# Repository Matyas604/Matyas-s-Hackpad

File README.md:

# Matyas-s-Hackpad
It has 8 keys (7 switches + rotary encoder switch), a rotary encoder, and an OLED display. Each key is backlit with SK6812 MINI-E LEDs. It uses [QMK](https://qmk.fm/) firmware and VIA.

## CAD Model:
Everything is connected by four M3x16mm screws and M3x5mx4mm heatset inserts. The case is printed in two parts, top and bottom.

<p align="center">
  <strong>Made in Fusion360</strong>
</p>

## PCB:
<p align="center">
  Schematic
</p>

<br>
<p align="center">
  PCB
</p>

<p align="center">
  <strong>Made in KiCad</strong>
</p>

## Case:

<p align="center">
  <strong>Made in Fusion360</strong>
</p>

## Firmware:
This Hackpad uses [QMK](https://qmk.fm/) firmware. Everything can be controlled in VIA. I have five layers set up, and I can assign anything to each one. I switch between them with a single switch. My layers are Main, Media, HA (shortcuts for Home Assistant), Game, and Other. I can also adjust the effects, speed, brightness, and backlight colors of LEDs directly from VIA. The OLED display shows the name of the current page.

## Final result:

<p align="center">
  <a href="https://www.youtube.com/shorts/VJYHFeJ_mRk">
    🎬 <b>HACKPAD DEMO HERE</b> 🎬
  </a>
</p>
I really enjoyed designing and building the hackpad. It was the very first project I designed from start to finish. I learned how to use Fusion and create PCBs in KiCAD. There were a few mistakes in the model, but they weren’t that big. I made only one mistake during assembly: I soldered the rotary encoder on the other side of the board, and when I desoldered it, I snapped off a leg, but there were two in the kit, so it was fine. The programming was a bit difficult, but in the end, I managed to do what I wanted. 

## BOM:
Here is everything you need to create this Hackpad:
| Component | Amount |
| :--- | :---: |
| **Seeed XIAO RP2040** | 1x |
| **MX-Style switches** | 7x |
| **1N4148 Diodes** | 8x | 
| **EC11 Rotary encoder** | 1x |
| **0.91 inch OLED display** | 1x |
| **DSA keycaps** | 7x |
| **SK6812 MINI-E LED** | 7x |
| **M3x16mm screw** | 4x |
| **M3x5mx4mm heatset insert** | 4x |
| **Case** (2 printed parts) | 1x |
| **PCB** | 1x |

<hr>

<p align="center">
  Made with ❤️ by <a href="https://github.com/Matyas604">@Matyas604</a>
</p>

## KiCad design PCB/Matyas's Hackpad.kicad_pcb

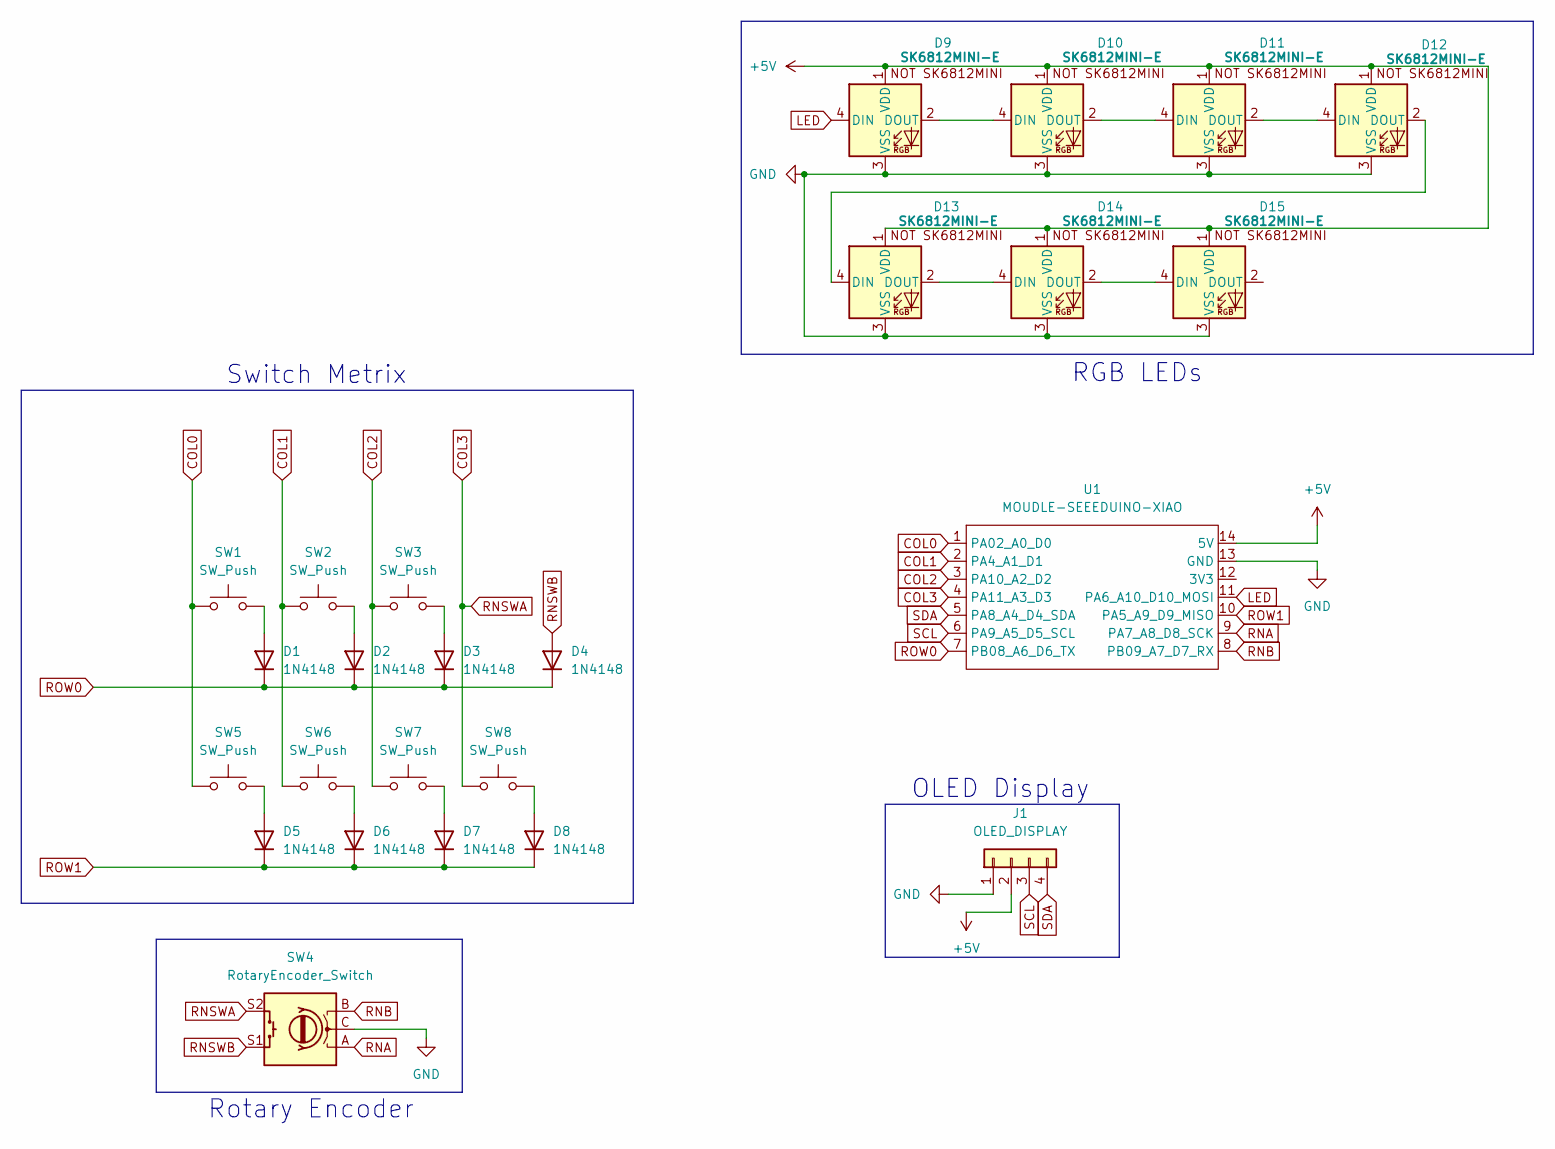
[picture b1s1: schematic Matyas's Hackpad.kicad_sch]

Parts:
D1, D2, D3, D4, D5, D6, D7, D8: 1N4148; D_DO-35_SOD27_P7.62mm_Horizontal
D9, D10, D11, D12, D13, D14, D15: SK6812MINI-E; SK6812MINI-E_fixed
J1: OLED_DISPLAY; SSD1306-0.91-OLED-4pin-128x32
SW1, SW2, SW3, SW5, SW6, SW7, SW8: SW_Push; SW_Cherry_MX_1.00u_PCB
SW4: RotaryEncoder_Switch; RotaryEncoder_Alps_EC11E-Switch_Vertical_H20mm
U1: MOUDLE-SEEEDUINO-XIAO; XIAO-Generic-Hybrid-14P-2.54-21X17.8MM

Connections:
+5V: D9.1 (VDD), D10.1 (VDD), D11.1 (VDD), D12.1 (VDD), D13.1 (VDD), D14.1 (VDD), D15.1 (VDD), J1.2, U1.14 (5V)
COL0: SW1.1, SW5.1, U1.1 (PA02_A0_D0)
COL1: SW2.1, SW6.1, U1.2 (PA4_A1_D1)
COL2: SW3.1, SW7.1, U1.3 (PA10_A2_D2)
COL3: SW4.S2, SW8.1, U1.4 (PA11_A3_D3)
GND: D9.3 (VSS), D10.3 (VSS), D11.3 (VSS), D12.3 (VSS), D13.3 (VSS), D14.3 (VSS), D15.3 (VSS), J1.1, SW4.C, U1.13 (GND)
LED: D9.4 (DIN), U1.11 (PA6_A10_D10_MOSI)
unnamed: D1.2 (A), SW1.2
unnamed: D2.2 (A), SW2.2
unnamed: D3.2 (A), SW3.2
unnamed: D5.2 (A), SW5.2
unnamed: D6.2 (A), SW6.2
unnamed: D7.2 (A), SW7.2
unnamed: D8.2 (A), SW8.2
unnamed: D9.2 (DOUT), D10.4 (DIN)
unnamed: D10.2 (DOUT), D11.4 (DIN)
unnamed: D11.2 (DOUT), D12.4 (DIN)
unnamed: D12.2 (DOUT), D13.4 (DIN)
unnamed: D13.2 (DOUT), D14.4 (DIN)
unnamed: D14.2 (DOUT), D15.4 (DIN)
RNA: SW4.A, U1.9 (PA7_A8_D8_SCK)
RNB: SW4.B, U1.8 (PB09_A7_D7_RX)
RNSWB: D4.2 (A), SW4.S1
ROW0: D1.1 (K), D2.1 (K), D3.1 (K), D4.1 (K), U1.7 (PB08_A6_D6_TX)
ROW1: D5.1 (K), D6.1 (K), D7.1 (K), D8.1 (K), U1.10 (PA5_A9_D9_MISO)
SCL: J1.3, U1.6 (PA9_A5_D5_SCL)
SDA: J1.4, U1.5 (PA8_A4_D4_SDA)

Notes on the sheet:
RGB LEDs
Switch Metrix
OLED Display
Rotary Encoder

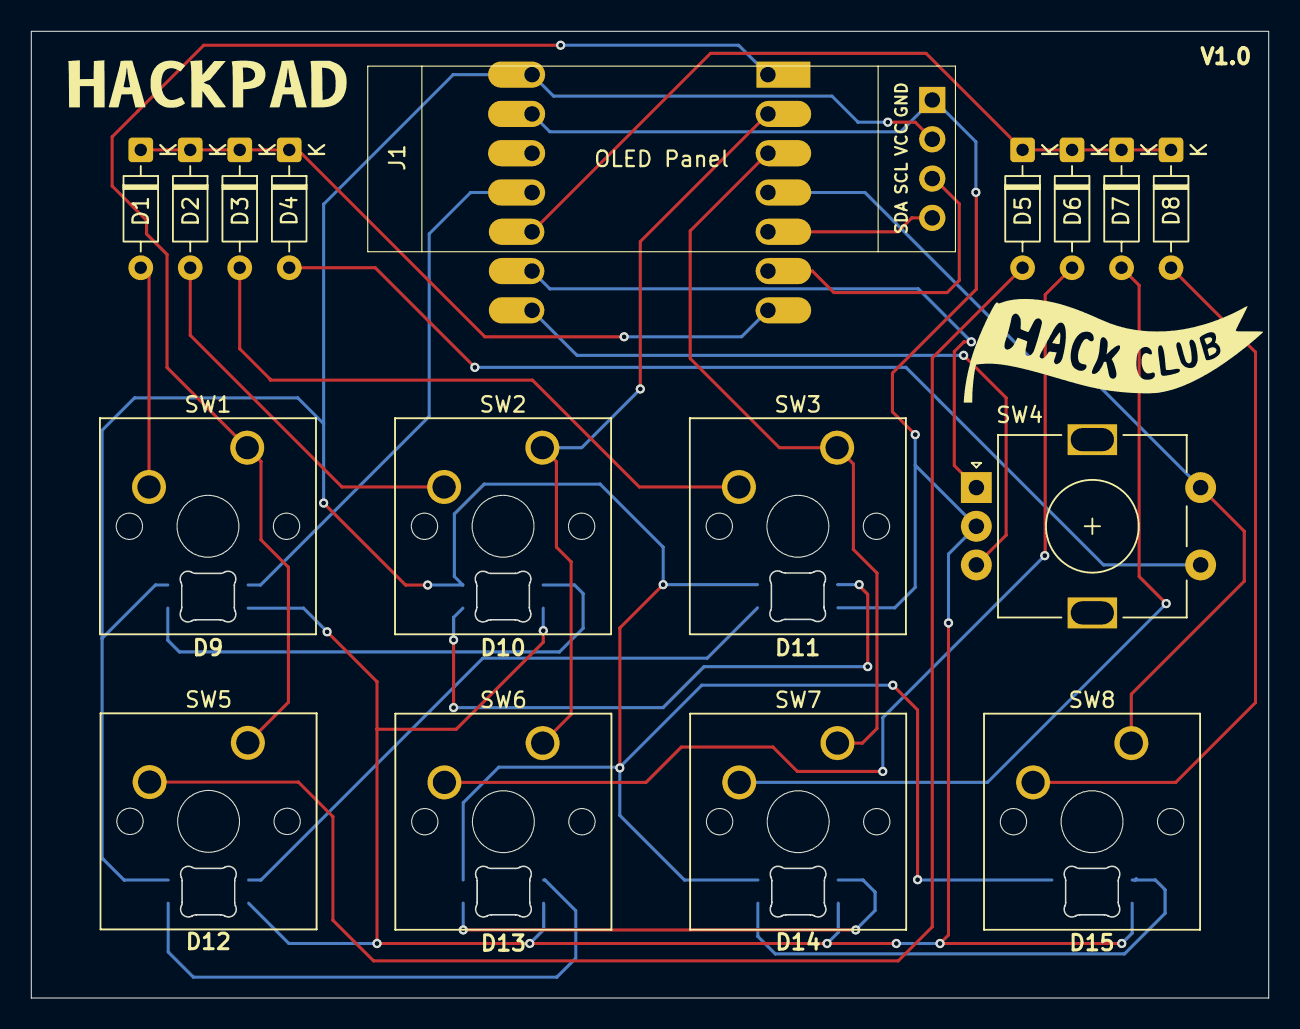
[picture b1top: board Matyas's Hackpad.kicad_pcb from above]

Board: 2 copper layers, 80.0 x 62.5 mm, 25 parts (1 on the bottom side), 27 nets.

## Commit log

2026-02-19 Create CAD
2026-02-19 Adding files
2026-02-20 Adding photos
2026-02-20 Update text
2026-02-20 Text update
2026-02-27 Change
2026-02-28 Fix for manufacture
2026-03-25 Adding json for VIA
2026-03-27 Adding photos of hackpad
2026-03-27 Firmware update
2026-03-27 Adding new firmware
2026-03-27 Adding VIA photos
2026-03-31 Adding Hackpad demo
2026-04-14 Create LICENSE
